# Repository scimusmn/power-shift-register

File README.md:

Power Shift Registers
=====================

Modular power shift register boards, based on the [TPIC6A595NE] chips.

These boards come in two varieties: *mother boards*, which include a Metro Mini and lack a data in port, and *daughter boards*, which are intended to have data shifted in to them. These two designs exist so that for applications that require only shift registers no additional hardware is necessary, but custom boards can still be designed to control the daughter boards.

[TPIC6A595NE]: https://www.ti.com/lit/ds/symlink/tpic6a595.pdf

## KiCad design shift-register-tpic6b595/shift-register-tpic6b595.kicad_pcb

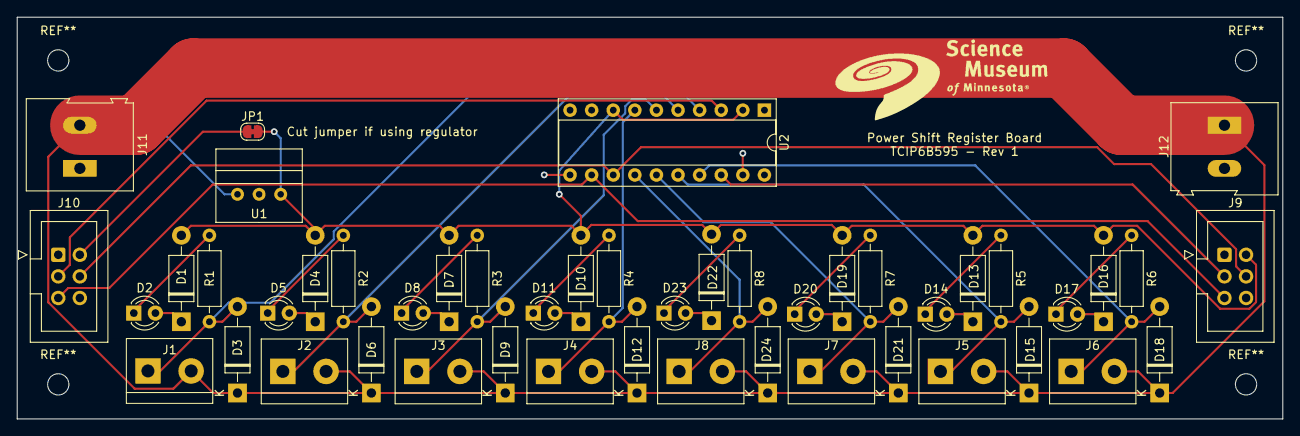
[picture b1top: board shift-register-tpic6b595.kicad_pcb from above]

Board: 2 copper layers, 148.8 x 47.2 mm, 47 parts (0 on the bottom side), 32 nets.

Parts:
D1, D3, D4, D6, D7, D9, D10, D12, D13, D15, D16, D18, D19, D21, D22, D24: 1N4001; D_DO-41_SOD81_P10.16mm_Horizontal
D2, D5, D8, D11, D14, D17, D20, D23: LED; LED_D3.0mm
J1, J2, J3, J4, J5, J6, J7, J8: Screw_Terminal_01x02; TerminalBlock_bornier-2_P5.08mm
J9, J10: Conn_02x03_Odd_Even; IDC-Header_2x03_P2.54mm_Vertical
J11, J12: Screw_Terminal_01x02; TerminalBlock-2_P5.08mm_large
JP1: SolderJumper_2_Bridged; SolderJumper-2_P1.3mm_Bridged_RoundedPad1.0x1.5mm
R1, R2, R3, R4, R5, R6, R7, R8: R; Resistor_L6.3mm_D2.5mm_P10.16mm_Horizontal
U1: I50115
U2: TPIC6B595; DIP-20_W7.62mm_Socket

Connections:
+5V: D1.2 (A), D4.2 (A), D7.2 (A), D10.2 (A), D13.2 (A), D16.2 (A), D19.2 (A), D22.2 (A), J9.2, JP1.2 (B), U1.3 (+5V), U2.2 (VCC), U2.8 (SRCLR)
+VDC: D3.1 (K), D6.1 (K), D9.1 (K), D12.1 (K), D15.1 (K), D18.1 (K), D21.1 (K), D24.1 (K), J1.2, J2.2, J3.2, J4.2, J5.2, J6.2, J7.2, J8.2, J11.2, J12.1, U1.1 (PWR)
/CLOCK: J9.4, J10.4, U2.13 (SRCK)
/D0: D3.2 (A), J1.1, R1.2, U2.4 (DRAIN0)
/D1: D6.2 (A), J2.1, R2.2, U2.5 (DRAIN1)
/D2: D9.2 (A), J3.1, R3.2, U2.6 (DRAIN2)
/D3: D12.2 (A), J4.1, R4.2, U2.7 (DRAIN3)
/D4: D24.2 (A), J8.1, R8.2, U2.14 (DRAIN4)
/D5: D21.2 (A), J7.1, R7.2, U2.15 (DRAIN5)
/D6: D15.2 (A), J5.1, R5.2, U2.16 (DRAIN6)
/D7: D18.2 (A), J6.1, R6.2, U2.17 (DRAIN7)
/LATCH: J9.5, J10.5, U2.12 (RCK)
/SERIN: J10.3, U2.3 (SERIN)
/SEROUT: J9.3, U2.18 (SEROUT)
GND: J9.1, J10.1, J11.1, J12.2, U1.2 (GND), U2.10 (GND), U2.11 (GND), U2.19 (GND)
unnamed: D1.1 (K), D2.2 (A)
unnamed: D2.1 (K), R1.1
unnamed: D4.1 (K), D5.2 (A)
unnamed: D5.1 (K), R2.1
unnamed: D7.1 (K), D8.2 (A)
unnamed: D8.1 (K), R3.1
unnamed: D10.1 (K), D11.2 (A)
unnamed: D11.1 (K), R4.1
unnamed: D13.1 (K), D14.2 (A)
unnamed: D14.1 (K), R5.1
unnamed: D16.1 (K), D17.2 (A)
unnamed: D17.1 (K), R6.1
unnamed: D19.1 (K), D20.2 (A)
unnamed: D20.1 (K), R7.1
unnamed: D22.1 (K), D23.2 (A)
unnamed: D23.1 (K), R8.1
unnamed: J10.2, JP1.1 (A)

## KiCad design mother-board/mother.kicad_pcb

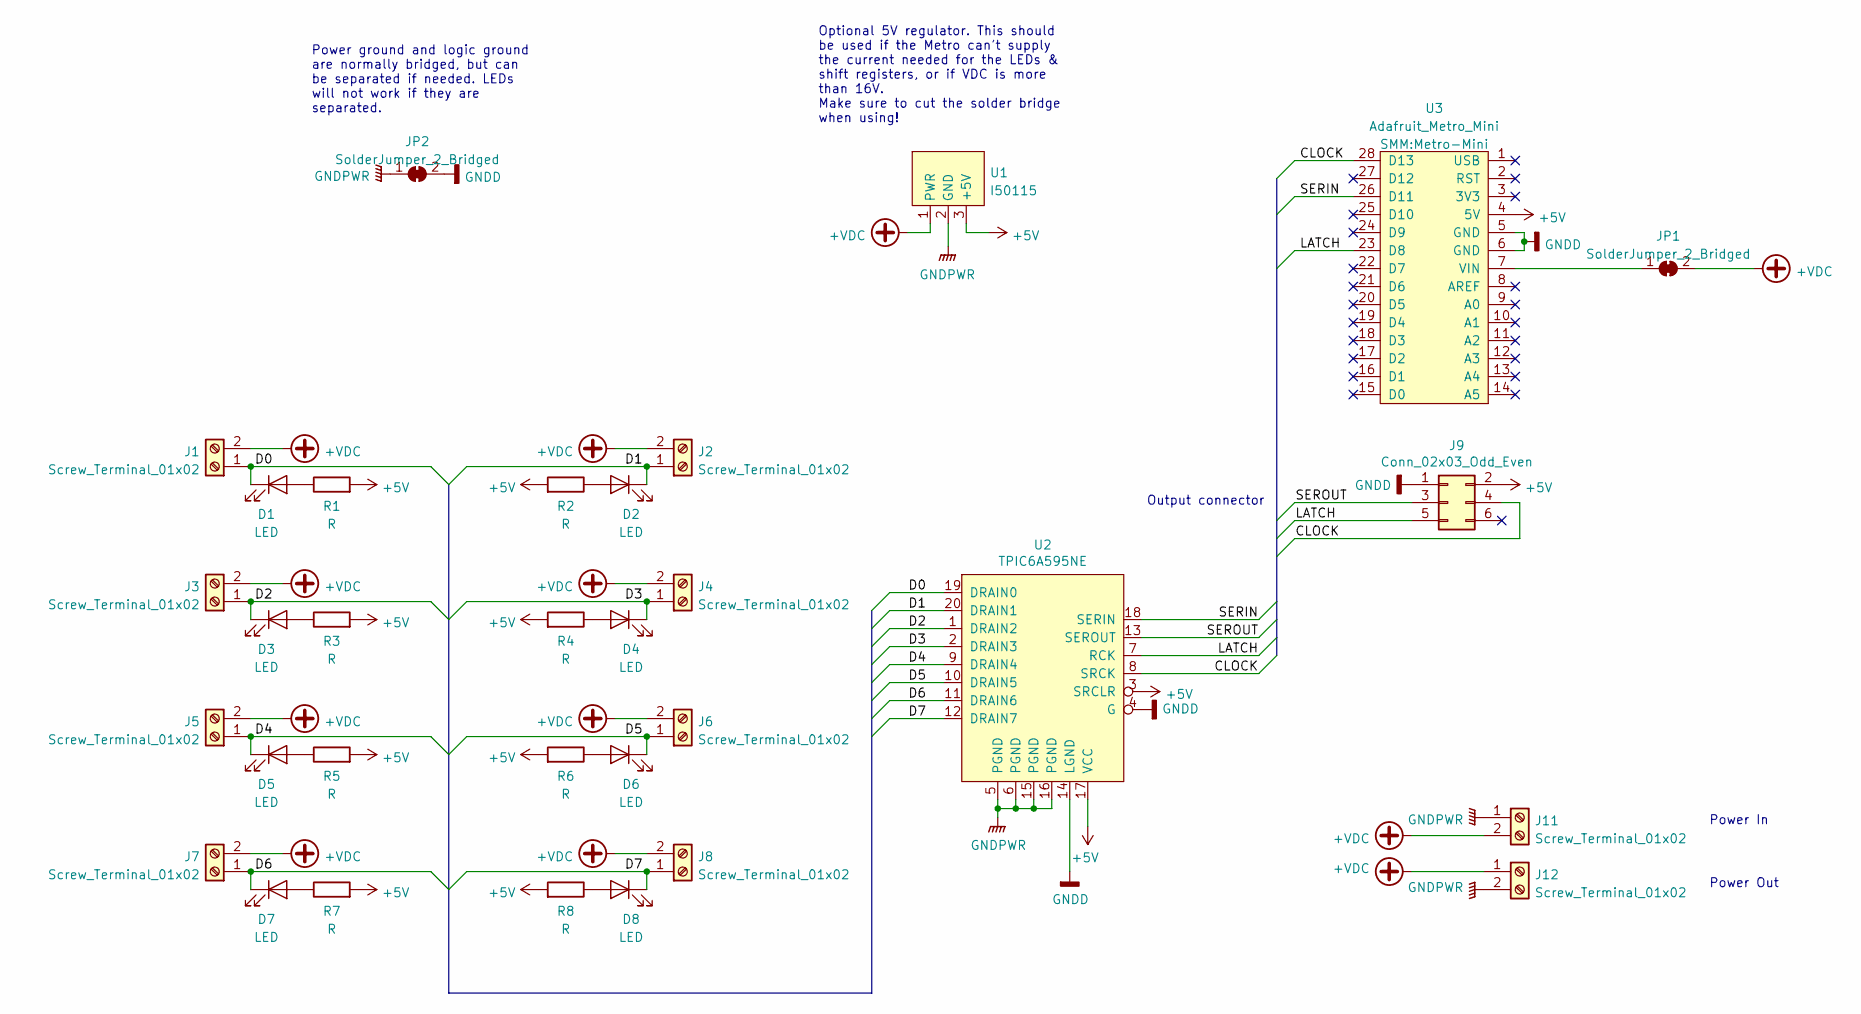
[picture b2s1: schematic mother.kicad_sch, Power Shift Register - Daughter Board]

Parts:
D1, D2, D3, D4, D5, D6, D7, D8: LED; LED_D3.0mm
J1, J2, J3, J4, J5, J6, J7, J8: Screw_Terminal_01x02; TerminalBlock_bornier-2_P5.08mm
J9: Conn_02x03_Odd_Even; IDC-Header_2x03_P2.54mm_Vertical
J11, J12: Screw_Terminal_01x02; TerminalBlock-2_P5.08mm_large
JP1, JP2: SolderJumper_2_Bridged; SolderJumper-2_P1.3mm_Bridged_RoundedPad1.0x1.5mm
R1, R2, R3, R4, R5, R6, R7, R8: R; R_Axial_DIN0207_L6.3mm_D2.5mm_P10.16mm_Horizontal
U1: I50115
U2: TPIC6A595NE; DIP-20_W7.62mm_Socket
U3: Adafruit_Metro_Mini; Metro-Mini

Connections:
+5V: J9.2, R1.2, R2.2, R3.2, R4.2, R5.2, R6.2, R7.2, R8.2, U1.3 (+5V), U2.3 (SRCLR), U2.17 (VCC), U3.4 (5V)
+VDC: J1.2, J2.2, J3.2, J4.2, J5.2, J6.2, J7.2, J8.2, J11.2, J12.1, JP1.2 (B), U1.1 (PWR)
/CLOCK: J9.4, U2.8 (SRCK), U3.28 (D13)
/D0: D1.1 (K), J1.1, U2.19 (DRAIN0)
/D1: D2.1 (K), J2.1, U2.20 (DRAIN1)
/D2: D3.1 (K), J3.1, U2.1 (DRAIN2)
/D3: D4.1 (K), J4.1, U2.2 (DRAIN3)
/D4: D5.1 (K), J5.1, U2.9 (DRAIN4)
/D5: D6.1 (K), J6.1, U2.10 (DRAIN5)
/D6: D7.1 (K), J7.1, U2.11 (DRAIN6)
/D7: D8.1 (K), J8.1, U2.12 (DRAIN7)
/LATCH: J9.5, U2.7 (RCK), U3.23 (D8)
/SERIN: U2.18 (SERIN), U3.26 (D11)
/SEROUT: J9.3, U2.13 (SEROUT)
GNDD: J9.1, JP2.2 (B), U2.4 (G), U2.14 (LGND), U3.5 (GND), U3.6 (GND)
GNDPWR: J11.1, J12.2, JP2.1 (A), U1.2 (GND), U2.5 (PGND), U2.6 (PGND), U2.15 (PGND), U2.16 (PGND)
unnamed: D1.2 (A), R1.1
unnamed: D2.2 (A), R2.1
unnamed: D3.2 (A), R3.1
unnamed: D4.2 (A), R4.1
unnamed: D5.2 (A), R5.1
unnamed: D6.2 (A), R6.1
unnamed: D7.2 (A), R7.1
unnamed: D8.2 (A), R8.1
unnamed: JP1.1 (A), U3.7 (VIN)

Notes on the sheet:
Power Out
Output connector
Power ground and logic ground are normally bridged, but can be separated if needed. LEDs will not work if they are separated.
Optional 5V regulator. This should be used if the Metro can't supply the current needed for the LEDs & shift registers, or if VDC is more than 16V. Make sure to cut the solder bridge when using!
Power In

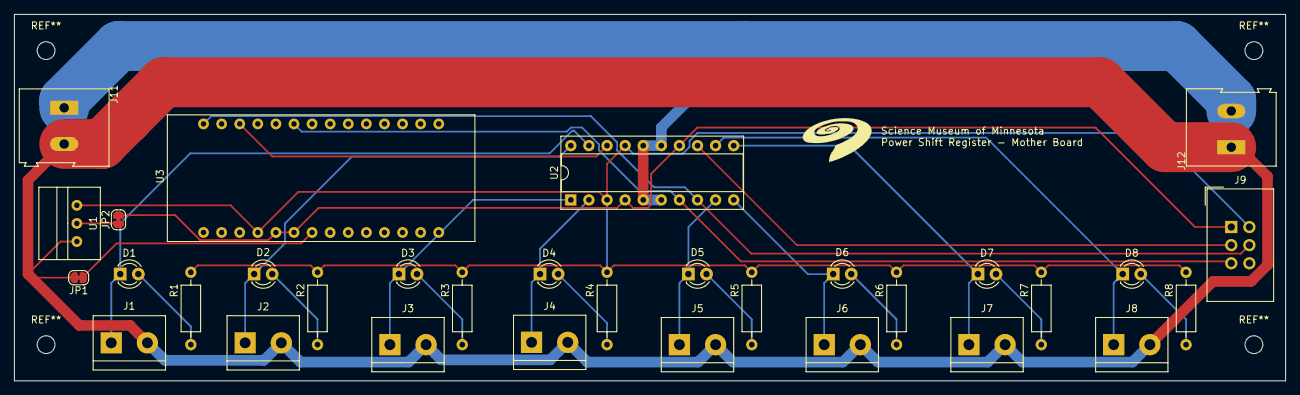
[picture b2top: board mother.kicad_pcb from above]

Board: 2 copper layers, 178.4 x 51.4 mm, 32 parts (0 on the bottom side), 25 nets.

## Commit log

2022-02-28 add README.md
2022-03-08 add basic mother schematic
2022-03-08 add all footprints and netlist
2022-03-18 add daughter board
2022-03-30 add rev 0 boards
2022-05-24 add tpic6b595 board
